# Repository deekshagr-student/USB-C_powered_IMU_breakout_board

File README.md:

# USB-C_powered_IMU_breakout_board
To power and interface the IMU on my Self Balancing Bot

# USB-C powered IMU breakout board
A small KiCad project: USB-C 5V input, regulated to 3.3V via an LDO, broken out to I2C for interfacing an MPU6050 IMU.

## Why
Built to power and interface the IMU on my Self-Balancing Robot project without relying on breadboard wiring.

## Design
- USB-C connector (power only, CC pulldowns (5.1k x2) for power negotiation)
- AMS1117-3.3 LDO regulator with input/output decoupling
- I2C breakout header (SDA, SCL, 3.3V, GND) with 4.7k pullups

## Process

To design a simple 2-layer PCB in KiCad that takes 5V USB-C input, regulates it down via an LDO, and breaks out I2C pins for a sensor (here, an IMU), the process from schematic to fabrication-ready files is as follows:

### Schematic

USB-C connector — chosen as the power input since it's the modern standard. It includes CC1/CC2 configuration channel pins, which signal to the power source (laptop, charger, etc.) that a valid device is present, enabling it to supply power. These pins are pulled down through 5.1k resistors so the source recognizes the connection.

LDO (Low Dropout Regulator) — a linear DC voltage regulator. Since the IMU's logic operates at 3.3V while USB-C supplies 5V, the LDO steps the voltage down. LDOs are well suited to small voltage drops like this, unlike larger step-downs which dissipate excess power as heat. Input and output capacitors (Cin, Cout) suppress voltage spikes and noise at the regulator's pins, ensuring a stable rail.

I2C (Inter-Integrated Circuit) — a communication protocol allowing multiple devices to share a single two-wire bus (SDA, SCL). I2C uses an open-drain design, meaning devices can only pull a line low, never drive it high — this prevents conflicts when multiple devices share the bus. Pull-up resistors (4.7k) are required to hold the lines high by default.

IMU module (MPU6050) — requires power, ground, and the two I2C lines. A solid ground connection is essential for reliable communication.

### PCB Design

Following the schematic, footprints were placed to keep routing paths short and direct. Using the ratsnest as a guide, appropriate trace widths were assigned — 10 mil for SDA/SCL signal lines, 20 mil for VCC/3V3/GND power lines. Routing was completed across two copper layers: B.Cu dedicated to GND (as a filled zone), and F.Cu for all other nets.

## Status
- [x] Schematic
- [x] PCB layout
- [x] Gerber files

## Tools
KiCad 8.x

## License
MIT (or your choice)

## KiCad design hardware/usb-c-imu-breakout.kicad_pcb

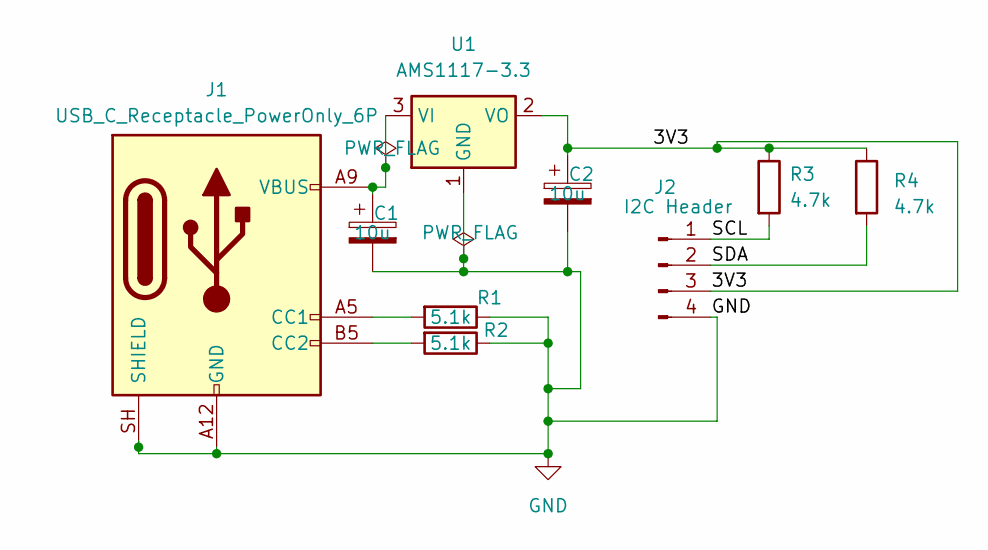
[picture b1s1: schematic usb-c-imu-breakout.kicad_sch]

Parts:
C1, C2: 10u; CP_Elec_4x3
J1: USB_C_Receptacle_PowerOnly_6P; USB_C_Receptacle_GCT_USB4115-03-C
J2: I2C Header; PinSocket_1x04_P2.54mm_Vertical
R1, R2: 5.1k; R_0805_2012Metric
R3, R4: 4.7k; R_0805_2012Metric
U1: AMS1117-3.3; SOT-223-3_TabPin2

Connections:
/3V3: C2.1, J2.3, R3.1, R4.1, U1.2 (VO)
/SCL: J2.1, R3.2
/SDA: J2.2, R4.2
GND: C1.2, C2.2, J1.A12 (GND), J1.B12 (GND), J1.SH (SHIELD), J2.4, R1.1, R2.1, U1.1 (GND)
unnamed: J1.A5 (CC1), R1.2
unnamed: J1.B5 (CC2), R2.2
unnamed: C1.1, J1.A9 (VBUS), J1.B9 (VBUS), U1.3 (VI)

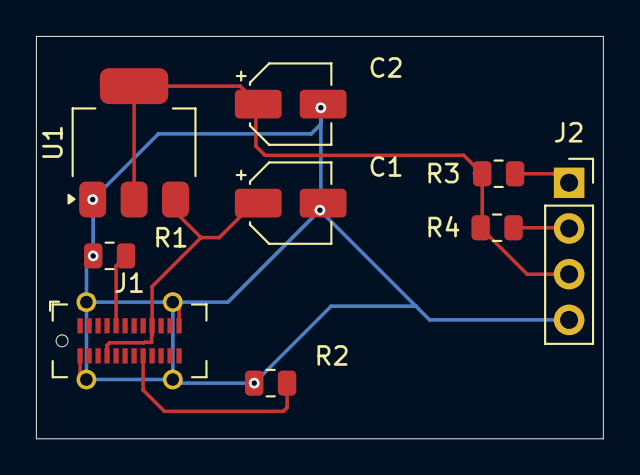
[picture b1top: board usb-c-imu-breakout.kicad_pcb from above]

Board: 2 copper layers, 31.5 x 22.4 mm, 9 parts (0 on the bottom side), 7 nets.
